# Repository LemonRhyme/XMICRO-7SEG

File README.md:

# XMICRO-7SEG

Simple LED display card for the XMICRO bus, featuring a 16-byte hexadecimal
display and a 10-bit bar graph.

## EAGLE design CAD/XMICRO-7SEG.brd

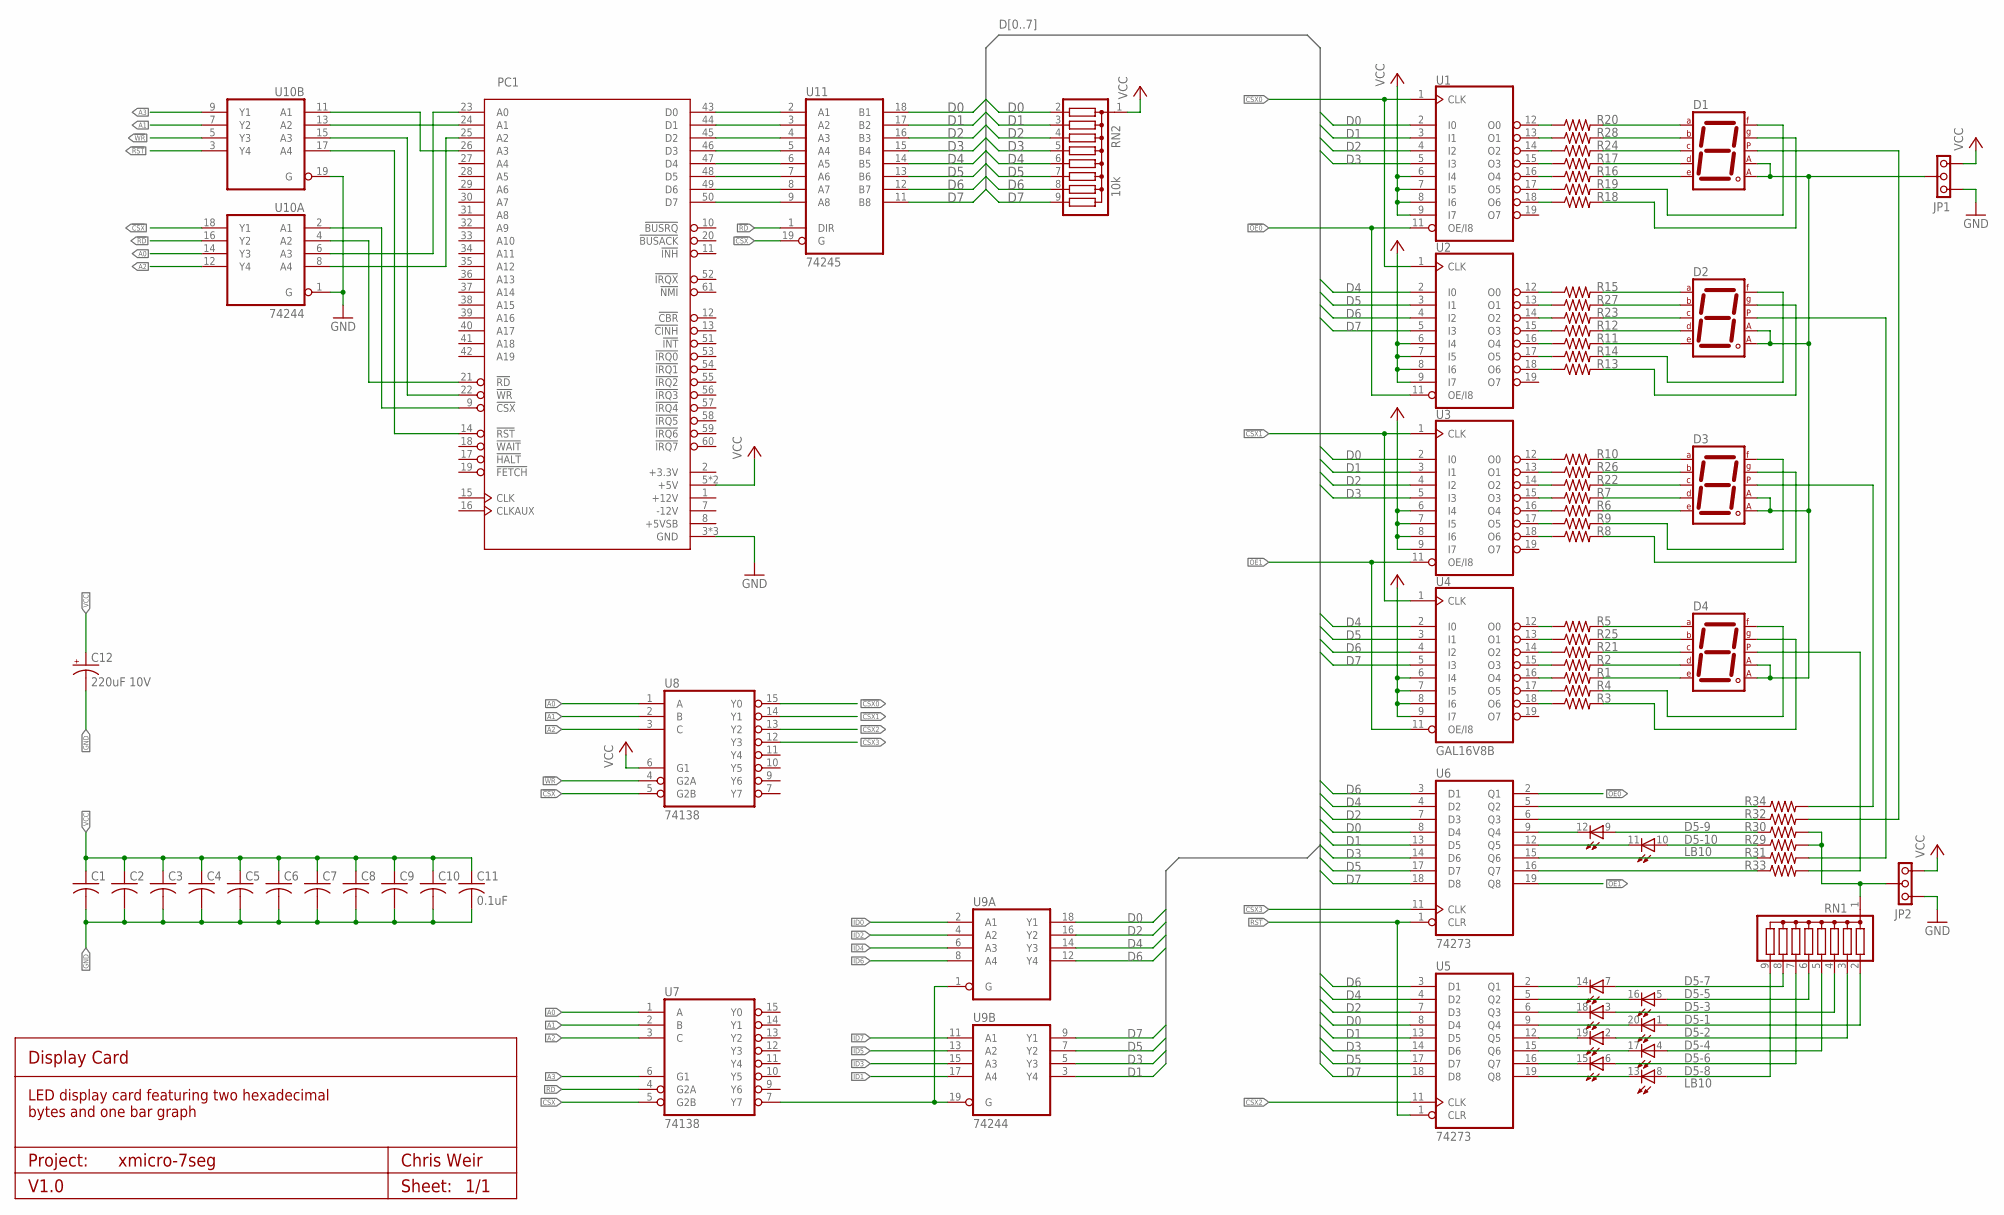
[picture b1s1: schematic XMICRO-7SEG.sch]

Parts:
C1, C2, C3, C4, C5, C6, C7, C8, C9, C10, C11: 0.1uF; C025-024X044
C12: 220uF 10V; C-10-5
D1, D2, D3, D4: 7SEG-CA; 7SEG-13
D5: LB10
JP1, JP2: PINHD1X3THRU; 1X03
PC1: XMICRO-BUS-EDGE62M; EDGE62M
R1, R2, R3, R4, R5, R6, R7, R8, R9, R10, R11, R12, R13, R14, R15, R16, R17, R18, R19, R20, R21, R22, R23, R24, R25, R26, R27, R28, R29, R30, R31, R32, R33, R34: R-US_0207/10; 0207/10
RN1: G08R; SIL9
RN2: 10k; SIL9
U1, U2, U3, U4: GAL16V8B; DIL20
U5, U6: 74273; DIL20
U7, U8: 74138; DIL16
U9, U10: 74244; DIL20
U11: 74245; DIL20

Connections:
!CSX: U7.5 (G2B), U8.5 (G2B), U10.18 (Y1), U11.19 (G)
!CSX0: U1.1 (CLK), U2.1 (CLK), U8.15 (Y0)
!CSX1: U3.1 (CLK), U4.1 (CLK), U8.14 (Y1)
!CSX2: U5.11 (CLK), U8.13 (Y2)
!CSX3: U6.11 (CLK), U8.12 (Y3)
!OE0: U1.11 (OE/I8), U2.11 (OE/I8), U6.2 (Q1)
!OE1: U3.11 (OE/I8), U4.11 (OE/I8), U6.19 (Q8)
!RD: U7.4 (G2A), U10.16 (Y2), U11.1 (DIR)
!RST: U5.1 (CLR), U6.1 (CLR), U10.3 (Y4)
!WR: U8.4 (G2A), U10.5 (Y3)
A0: U7.1 (A), U8.1 (A), U10.14 (Y3)
A1: U7.2 (B), U8.2 (B), U10.7 (Y2)
A2: U7.3 (C), U8.3 (C), U10.12 (Y4)
A3: U7.6 (G1), U10.9 (Y1)
D0: RN2.2, U1.2 (I0), U3.2 (I0), U5.8 (D4), U6.8 (D4), U9.18 (Y1), U11.18 (B1)
D1: RN2.3, U1.3 (I1), U3.3 (I1), U5.13 (D5), U6.13 (D5), U9.3 (Y4), U11.17 (B2)
D2: RN2.4, U1.4 (I2), U3.4 (I2), U5.7 (D3), U6.7 (D3), U9.16 (Y2), U11.16 (B3)
D3: RN2.5, U1.5 (I3), U3.5 (I3), U5.14 (D6), U6.14 (D6), U9.5 (Y3), U11.15 (B4)
D4: RN2.6, U2.2 (I0), U4.2 (I0), U5.4 (D2), U6.4 (D2), U9.14 (Y3), U11.14 (B5)
D5: RN2.7, U2.3 (I1), U4.3 (I1), U5.17 (D7), U6.17 (D7), U9.7 (Y2), U11.13 (B6)
D6: RN2.8, U2.4 (I2), U4.4 (I2), U5.3 (D1), U6.3 (D1), U9.12 (Y4), U11.12 (B7)
D7: RN2.9, U2.5 (I3), U4.5 (I3), U5.18 (D8), U6.18 (D8), U9.9 (Y1), U11.11 (B8)
GND: C1.2, C2.2, C3.2, C4.2, C5.2, C6.2, C7.2, C8.2, C9.2, C10.2, C11.2, C12.-, JP1.1, JP2.1, PC1.3 (GND), PC1.4 (GND), PC1.62 (GND), U1.10 (GND), U2.10 (GND), U3.10 (GND), U4.10 (GND), U5.10 (GND), U6.10 (GND), U7.8 (GND), U8.8 (GND), U9.10 (GND), U10.1 (G), U10.10 (GND), U10.19 (G), U11.10 (GND)
ID0: U9.2 (A1)
ID1: U9.17 (A4)
ID2: U9.4 (A2)
ID3: U9.15 (A3)
ID4: U9.6 (A3)
ID5: U9.13 (A2)
ID6: U9.8 (A4)
ID7: U9.11 (A1)
unnamed: D5.12 (C), U6.9 (Q4)
unnamed: D5.11 (C), U6.12 (Q5)
unnamed: R32.1, U6.6 (Q3)
unnamed: R31.1, U6.15 (Q6)
unnamed: R33.1, U6.16 (Q7)
unnamed: D5.1 (A), RN1.2
unnamed: D5.2 (A), RN1.3
unnamed: D5.3 (A), RN1.4
unnamed: D5.4 (A), RN1.5
unnamed: D5.5 (A), RN1.6
unnamed: D5.6 (A), RN1.7
unnamed: D5.7 (A), RN1.8
unnamed: D5.8 (A), RN1.9
unnamed: D5.20 (C), U5.9 (Q4)
unnamed: D5.19 (C), U5.12 (Q5)
unnamed: D5.18 (C), U5.6 (Q3)
unnamed: D5.17 (C), U5.15 (Q6)
unnamed: D5.16 (C), U5.5 (Q2)
unnamed: R5.1, U4.12 (O0)
unnamed: R25.1, U4.13 (O1)
unnamed: R21.1, U4.14 (O2)
unnamed: R2.1, U4.15 (O3)
unnamed: R1.1, U4.16 (O4)
unnamed: R4.1, U4.17 (O5)
unnamed: R34.1, U6.5 (Q2)
unnamed: PC1.43 (D0), U11.2 (A1)
unnamed: R3.1, U4.18 (O6)
unnamed: D4.7 (A), R5.2
unnamed: D4.6 (B), R25.2
unnamed: D4.4 (C), R21.2
unnamed: D1.3 (CA1), D1.8 (CA2), D2.3 (CA1), D2.8 (CA2), D3.3 (CA1), D3.8 (CA2), D4.3 (CA1), D4.8 (CA2), JP1.2
unnamed: D5.15 (C), U5.16 (Q7)
unnamed: D5.14 (C), U5.2 (Q1)
unnamed: D5.13 (C), U5.19 (Q8)
unnamed: D4.2 (D), R2.2
unnamed: D4.1 (E), R1.2
unnamed: D4.9 (F), R4.2
unnamed: D4.10 (G), R3.2
unnamed: PC1.44 (D1), U11.3 (A2)
unnamed: PC1.45 (D2), U11.4 (A3)
unnamed: D5.9 (A), R30.1
unnamed: D5.10 (A), R29.1
unnamed: PC1.46 (D3), U11.5 (A4)
unnamed: PC1.47 (D4), U11.6 (A5)
unnamed: PC1.48 (D5), U11.7 (A6)
unnamed: D4.5 (DP), R33.2
unnamed: R10.1, U3.12 (O0)
unnamed: R26.1, U3.13 (O1)
unnamed: R22.1, U3.14 (O2)
unnamed: R7.1, U3.15 (O3)
unnamed: R6.1, U3.16 (O4)
unnamed: R9.1, U3.17 (O5)
unnamed: R8.1, U3.18 (O6)
unnamed: D3.7 (A), R10.2
unnamed: D3.6 (B), R26.2
unnamed: D3.4 (C), R22.2
unnamed: D3.2 (D), R7.2
unnamed: D3.1 (E), R6.2
unnamed: D3.9 (F), R9.2
unnamed: D3.10 (G), R8.2
unnamed: PC1.49 (D6), U11.8 (A7)
unnamed: PC1.50 (D7), U11.9 (A8)
unnamed: PC1.9 (!CSX), U10.2 (A1)
unnamed: PC1.14 (!RST), U10.17 (A4)
unnamed: PC1.21 (!RD), U10.4 (A2)
unnamed: PC1.22 (!WR), U10.15 (A3)
unnamed: R15.1, U2.12 (O0)
unnamed: R27.1, U2.13 (O1)
unnamed: R23.1, U2.14 (O2)
unnamed: R12.1, U2.15 (O3)
unnamed: R11.1, U2.16 (O4)
unnamed: R14.1, U2.17 (O5)
unnamed: R13.1, U2.18 (O6)
unnamed: D2.7 (A), R15.2
unnamed: D2.6 (B), R27.2
unnamed: D2.4 (C), R23.2
unnamed: D2.2 (D), R12.2
unnamed: D2.1 (E), R11.2
unnamed: D2.9 (F), R14.2
unnamed: D2.10 (G), R13.2
unnamed: PC1.23 (A0), U10.6 (A3)
unnamed: PC1.24 (A1), U10.13 (A2)
unnamed: PC1.25 (A2), U10.8 (A4)
unnamed: PC1.26 (A3), U10.11 (A1)
unnamed: U7.7 (Y7), U9.1 (G), U9.19 (G)
unnamed: JP2.2, R29.2, R30.2, RN1.1
unnamed: R20.1, U1.12 (O0)
unnamed: R28.1, U1.13 (O1)
unnamed: R24.1, U1.14 (O2)
unnamed: R17.1, U1.15 (O3)
unnamed: R16.1, U1.16 (O4)
unnamed: R19.1, U1.17 (O5)
unnamed: R18.1, U1.18 (O6)
unnamed: D1.7 (A), R20.2
unnamed: D1.6 (B), R28.2
unnamed: D1.4 (C), R24.2
unnamed: D1.2 (D), R17.2
unnamed: D1.1 (E), R16.2
unnamed: D1.9 (F), R19.2
unnamed: D1.10 (G), R18.2
unnamed: D3.5 (DP), R34.2
unnamed: D2.5 (DP), R31.2
unnamed: D1.5 (DP), R32.2
VCC: C1.1, C2.1, C3.1, C4.1, C5.1, C6.1, C7.1, C8.1, C9.1, C10.1, C11.1, C12.+, JP1.3, JP2.3, PC1.5 (+5V), PC1.6 (+5V), RN2.1, U1.6 (I4), U1.7 (I5), U1.8 (I6), U1.9 (I7), U1.20 (VCC), U2.6 (I4), U2.7 (I5), U2.8 (I6), U2.9 (I7), U2.20 (VCC), U3.6 (I4), U3.7 (I5), U3.8 (I6), U3.9 (I7), U3.20 (VCC), U4.6 (I4), U4.7 (I5), U4.8 (I6), U4.9 (I7), U4.20 (VCC), U5.20 (VCC), U6.20 (VCC), U7.16 (VCC), U8.6 (G1), U8.16 (VCC), U9.20 (VCC), U10.20 (VCC), U11.20 (VCC)

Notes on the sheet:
Display Card
LED display card featuring two hexadecimal bytes and one bar graph
Project:
V1.0
Chris Weir
Sheet:

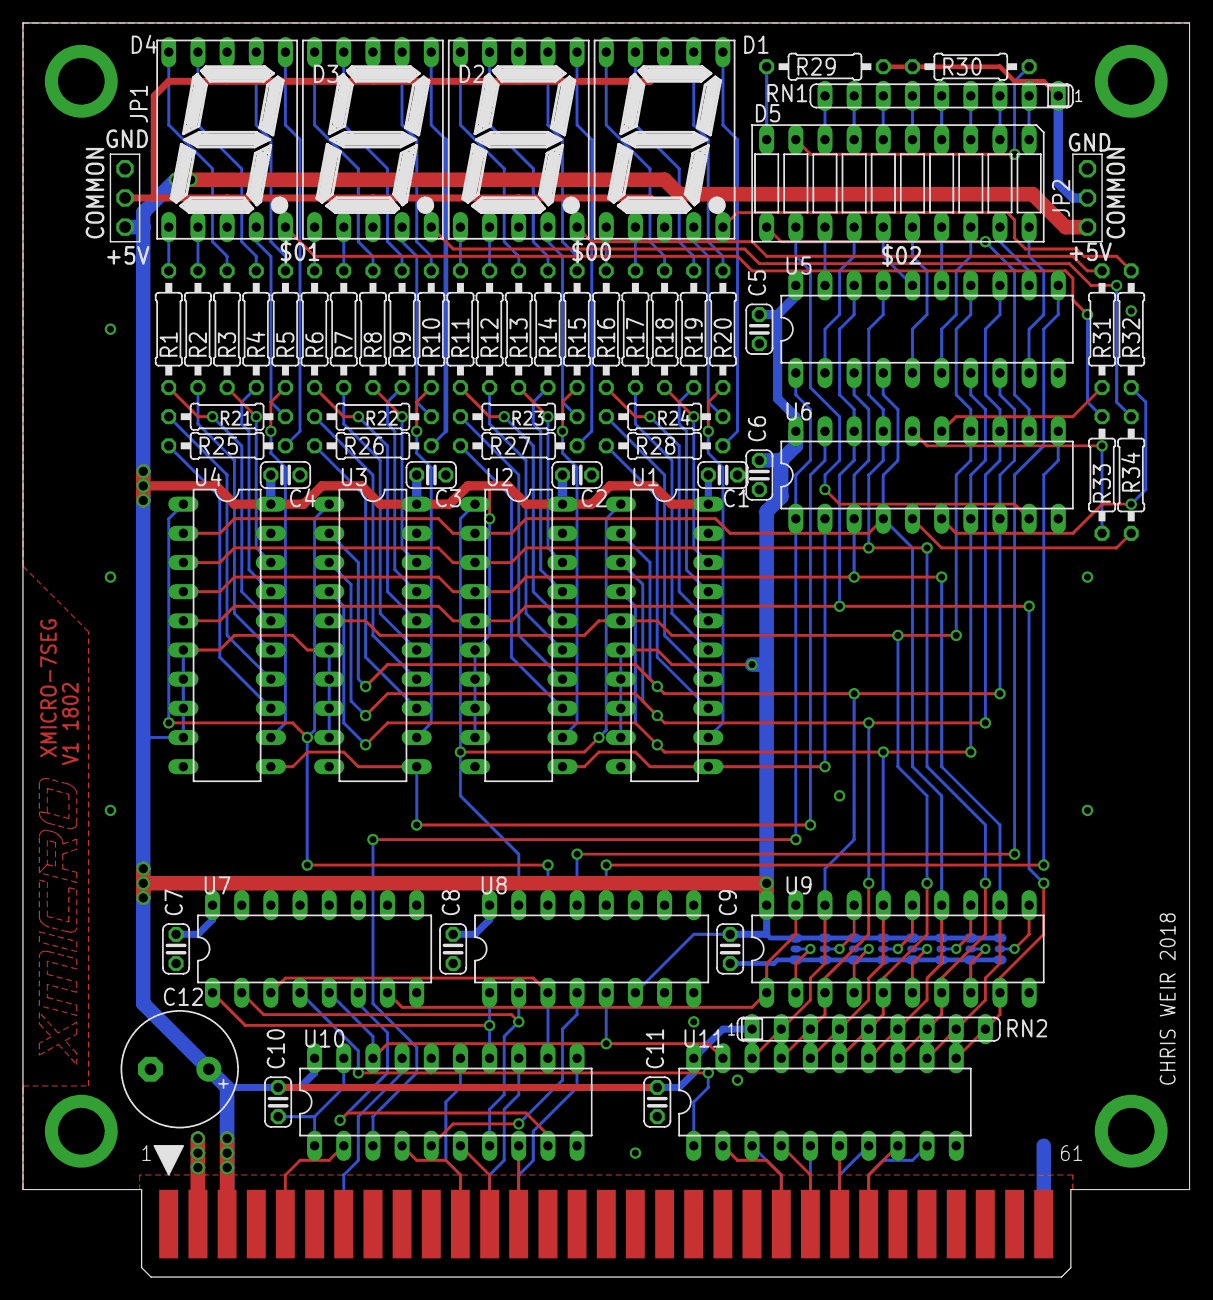
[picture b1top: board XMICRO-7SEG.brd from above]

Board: 2 copper layers, 101.6 x 109.2 mm, 67 parts (0 on the bottom side), 127 nets.

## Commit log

2018-08-16 Updated the name in the license
2019-05-28 Updated schematic xrefs to indicate signal direction.
2019-05-28 Added GAL code and binaries
2020-08-30 Added picture and updated README.md
